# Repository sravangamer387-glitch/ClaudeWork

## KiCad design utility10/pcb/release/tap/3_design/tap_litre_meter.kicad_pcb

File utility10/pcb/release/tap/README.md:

# Tap Litre Meter - main board (rev B)

Tap litre meter: hall flow sensor, pulse counting, OLED display, target alarm, 3 x AA.

**Status: engineering release, software-verified only (ERC on the netlist, KiCad DRC, netlist cross-check, SPICE where noted). Not yet built, not reviewed by a second engineer, not certified.**

## Specification
- Board 68 x 46 mm, 2 layers, 1.6 mm FR-4, 1 oz copper, rounded corners R2.5 mm, 4 x M2.5 mounting holes, 2 fiducials.
- Rules used: min track 0.2 mm (power 0.4 mm), min clearance 0.2 mm, via 0.6/0.3 mm, GND pour on both layers, 69 stitching vias.
- Finish: ENIG recommended (HASL lead-free acceptable); green mask, white silk; IPC class 2.
- 28 parts, 19 nets.

## Circuit description
- Flow pulses on INT1 (PD3) with 10 k pull-up, 100 nF filter, 1 k series and TVS on the cable; OLED on I2C (4.7 k pull-ups) through a 4-pin JST.
- **The flow sensor must accept 3.5-24 V** (3 x AA falls to 3.6 V); calibrate pulses per litre with a 10 L bucket.

## Power
Idle in power-down, wake on pulses; display only while water flows plus 10 s: months of battery.

## Verification
| Check | Result |
|---|---|
| Electrical rule check on the netlist (own ERC: unconnected pins, single-pin nets, output conflicts, unpowered supplies, symbol/footprint pin match) | 0 errors, 0 warnings |
| KiCad DRC | 0 errors, 0 warnings; unconnected pads: 0 |
| Schematic netlist equals PCB netlist | yes |
| Router failures | 0 |
| 3D STEP export | yes |
| Independent Gerber parse (gerbonara): layers parsed, outline size equals the design | 9 layers, outline [68.1, 46.1] mm, match |

Enclosure (prototype shell for 3D printing): outer 84.0 x 74.3 x 39.8 mm, collision/opening check: pass

## Bill of materials
| Ref | Value | Footprint | Manufacturer part | LCSC # | LCSC status |
|---|---|---|---|---|---|
| U1 | ATmega328P-AU | TQFP-32_7x7mm_P0.8mm | ATMEGA328P-AU | C14877 | verified |
| C1 | 100n | C_0603_1608Metric | Samsung CL10B104KB8NNNC 0603 100nF X7R 50V | C1591 | verified |
| C2 | 100n | C_0603_1608Metric | Samsung CL10B104KB8NNNC 0603 100nF X7R 50V | C1591 | verified |
| C3 | 100n | C_0603_1608Metric | Samsung CL10B104KB8NNNC 0603 100nF X7R 50V | C1591 | verified |
| R7 | 10k | R_0603_1608Metric | 0603 10k 1% | C25804 | verified |
| J2 | ISP | PinHeader_2x03_P2.54mm_Vertical | HCTL PZ254-2-03-Z-8.5 (ZHOURI C5116479 had only 340 in stock) | C2894964 | verified |
| J1 | BATT 3xAA | JST_PH_B2B-PH-K_1x02_P2.00mm_Vertical | JST B2B-PH-K-S(LF)(SN) | C131337 | verified |
| SW1 | Power | SW_SPDT_PCM12 | C&K PCM12SMTR | C221841 | verified |
| Q2 | AO3401A | SOT-23 | AO3401A | C15127 | verified |
| C4 | 10u | C_0805_2012Metric | 0805 10uF X5R | C15850 | verified |
| BZ1 | Buzzer | Buzzer_12x9.5RM7.6 | YUEXIN KC1206 16 ohm passive magnetic 12x9.5 mm (2048 Hz) | C781869 | verified |
| Q1 | MMBT3904 | SOT-23 | MMBT3904 | C20526 | verified |
| D2 | 1N4148WS | D_SOD-323 | 1N4148WS | C2128 | verified |
| R6 | 1k | R_0603_1608Metric | 0603 1k 1% | C21190 | verified |
| D1 | Green | LED_0603_1608Metric | Hubei KENTO KT-0603YG yellow-green 570 nm, Vf about 2 V (lights well from 3.3 V with 1 k; the Everlight 19-217 green was out of stock) | C2289 | verified |
| R5 | 1k | R_0603_1608Metric | 0603 1k 1% | C21190 | verified |
| SW2 | Reset / target | SW_SPST_B3U-1000P | Omron B3U-1000P | C231329 | verified |
| J3 | Flow sensor | JST_PH_B3B-PH-K_1x03_P2.00mm_Vertical | JST B3B-PH-K-S(LF)(SN) | C131339 | verified |
| R8 | 1k | R_0603_1608Metric | 0603 1k 1% | C21190 | verified |
| R9 | 10k | R_0603_1608Metric | 0603 10k 1% | C25804 | verified |
| C9 | 100n | C_0603_1608Metric | Samsung CL10B104KB8NNNC 0603 100nF X7R 50V | C1591 | verified |
| D4 | TVS 5V bidir | D_SOD-323 | Nexperia PESD5V0S1BA,115 | C19224 | verified |
| J4 | OLED 0.91in I2C | JST_PH_B4B-PH-K_1x04_P2.00mm_Vertical | JST B4B-PH-K-S(LF)(SN) | C131334 | verified |
| R10 | 4.7k | R_0603_1608Metric | 0603 4.7k 1% | C23162 | verified |
| R11 | 4.7k | R_0603_1608Metric | 0603 4.7k 1% | C23162 | verified |
| TP1 | TP | TestPoint_Pad_D1.5mm |  |  |  |
| TP2 | TP | TestPoint_Pad_D1.5mm |  |  |  |
| TP3 | TP | TestPoint_Pad_D1.5mm |  |  |  |

`verified` = LCSC number confirmed by web search on 2026-10-31/11-01; `memory` = from my recollection, **check on lcsc.com before ordering**; empty = no number chosen (through-hole connectors, switches, buzzer, test points: hand-assembled or chosen by the buyer). `*_JLC_BOM.csv` / `*_JLC_CPL.csv` list only the parts with an LCSC number; JLCPCB rotation corrections (CPL) must be checked in their viewer.

## Assembly notes
- Reflow (JLCPCB SMT): all SMD parts with an LCSC number. Hand-solder: JST connectors, pin headers, buzzer, switches, test points as listed in the BOM. Fiducials and mounting holes are in the Gerbers.
- Polarity: LED cathode toward GND (silk marks), electrolytic none, diode D2 cathode to +V, Q2 orientation as footprint (SOT-23 pin 1 = gate).
- Programming: ISP header J2 (pin 1 = MISO, square pad). Flash the matching image from `utility10/firmware/release/`: Seeti Counter `4MHz/seeti_prod.hex` (production firmware: timer-triggered 16 kS/s ADC, scan mode to find the real whistle frequency, battery check), Rain Alert `8MHz/rain_alert.hex`, Bijli Meter Reader `8MHz/bijli_meter.hex` (demo-grade firmware, to be hardened).

## Bring-up and test
1. Blow/spin the sensor: FLOW (TP3) pulses; firmware counts.
2. Run 10 L from a calibrated bucket: adjust pulses-per-litre.

## Files
`1_fabrication/` Gerber + drill zip (upload to JLCPCB/any fab), fab notes, copper plot
`2_assembly/` JLC BOM + CPL (SMD parts JLC assembles), full BOM with LCSC numbers for every part, pick-and-place, assembly drawing
`3_design/` KiCad 7 project (pcb, schematic, libs), netlist, STEP model, schematic PDF, renders
`4_enclosure/` printable enclosure (base, screwed lid, battery door, plungers / light pipes / switch extensions) or a mounting plate for a bought IP65 box; dimensions and notes in enclosure.json
`5_verification/` DRC, ERC, verification and readiness reports

## Known limits and review checklist
- Layout was produced by a custom router and software placement; a human layout review (analog routing, ground returns, creepage, connector mechanics, silkscreen) is still required.
- Not verified: EMC, ESD (apart from TVS parts where fitted), thermal, real component tolerances, supplier stock/price, assembly house design-for-manufacture check (run JLCPCB's DFM check on the Gerbers).
- Firmware thresholds are placeholders to be calibrated on prototypes.

## Manufacturing readiness (automatic check)

| Check | Result |
|---|---|
| gerber layers and drill present | PASS |
| drc errors 0 | PASS |
| unconnected 0 | PASS |
| netlist matches schematic | PASS |
| erc errors 0 | PASS |
| independent gerber check clean | PASS |
| every part has lcsc number | PASS |
| every lcsc number verified | PASS |
| cpl rows equal jlc bom parts | PASS |
| step model | PASS |
| KiCad DRC warnings | 0 |
| **Order ready** | **YES** |

Order steps: (1) upload `1_fabrication/*_gerbers.zip`; (2) for assembly upload `2_assembly/*_JLC_BOM.csv` and `*_JLC_CPL.csv`, check the 3D/rotation preview for every polarised part (diodes, ICs, LEDs, electrolytics) because CPL rotations are generated, not hand-checked; (3) buy the through-hole parts listed in `*_BOM_full.csv` marked hand/THT and solder them; (4) re-check stock and the exact LCSC listing for every line before paying.

Limits: the layout is software-generated and has not been reviewed by a PCB engineer; no prototype has been built; the first batch should be treated as a prototype run (order 5 boards).

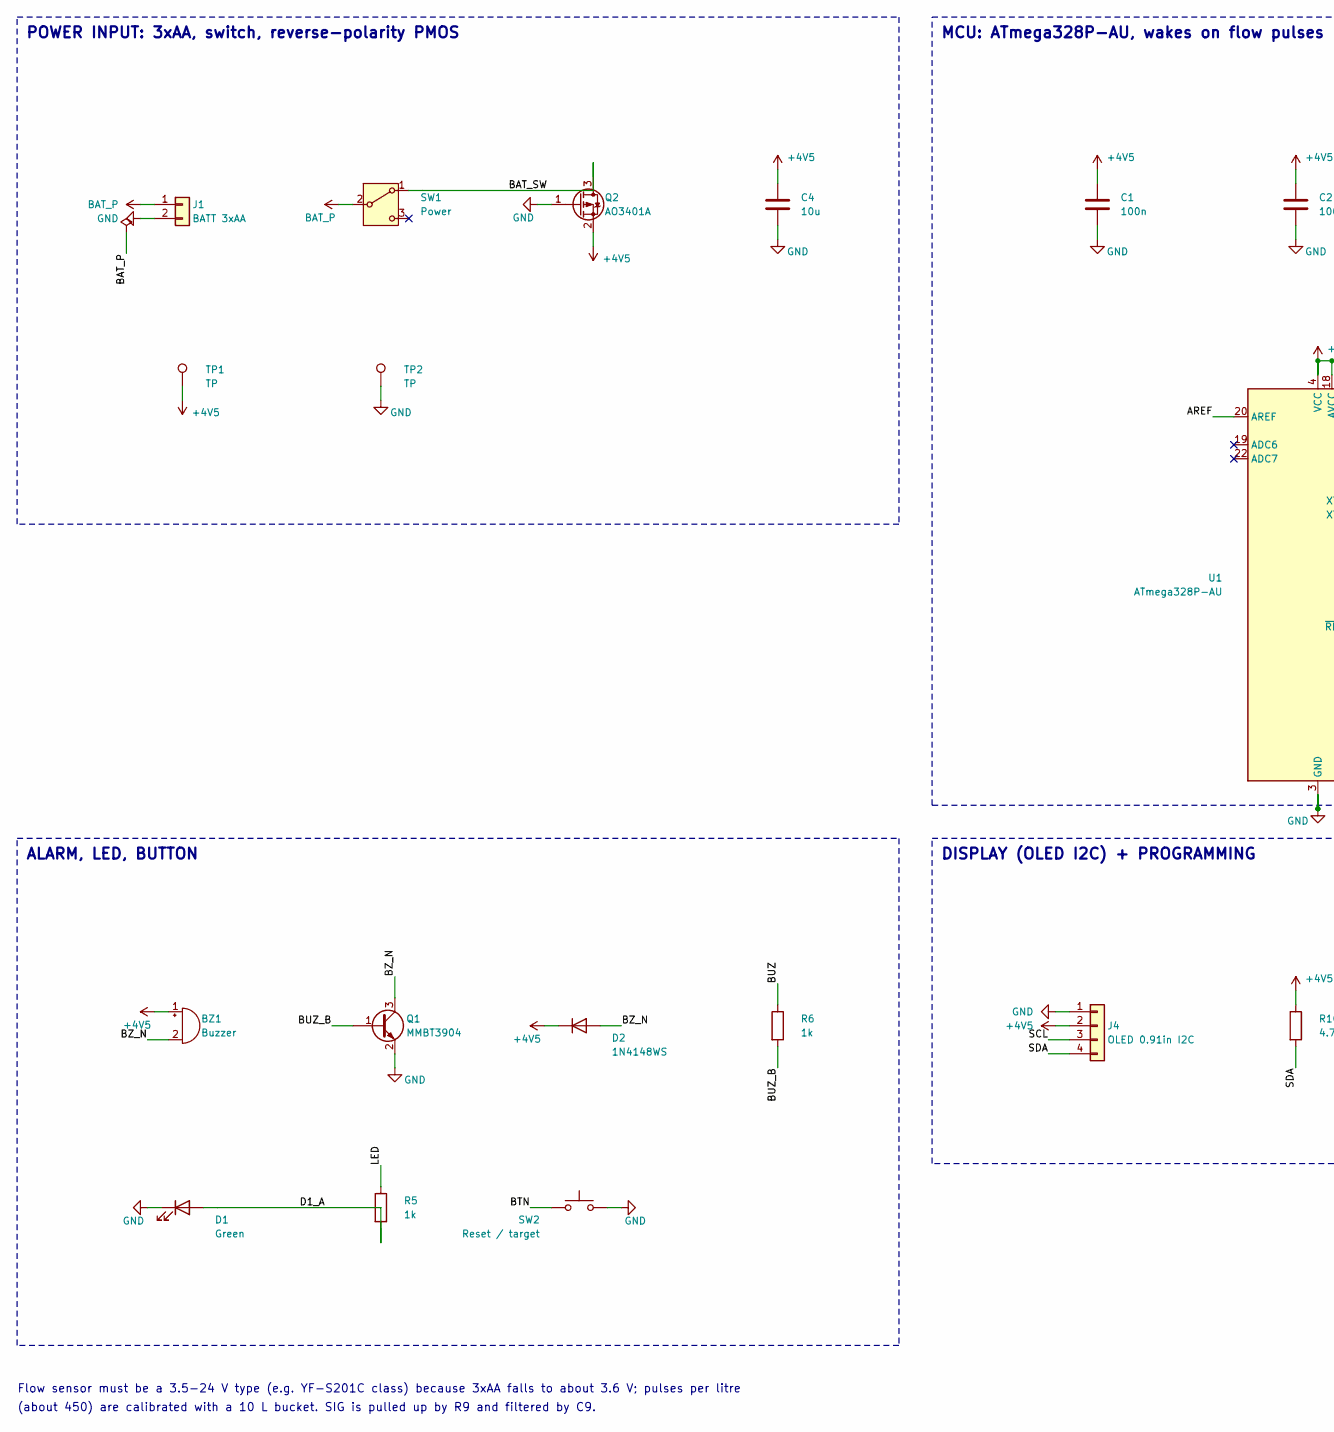
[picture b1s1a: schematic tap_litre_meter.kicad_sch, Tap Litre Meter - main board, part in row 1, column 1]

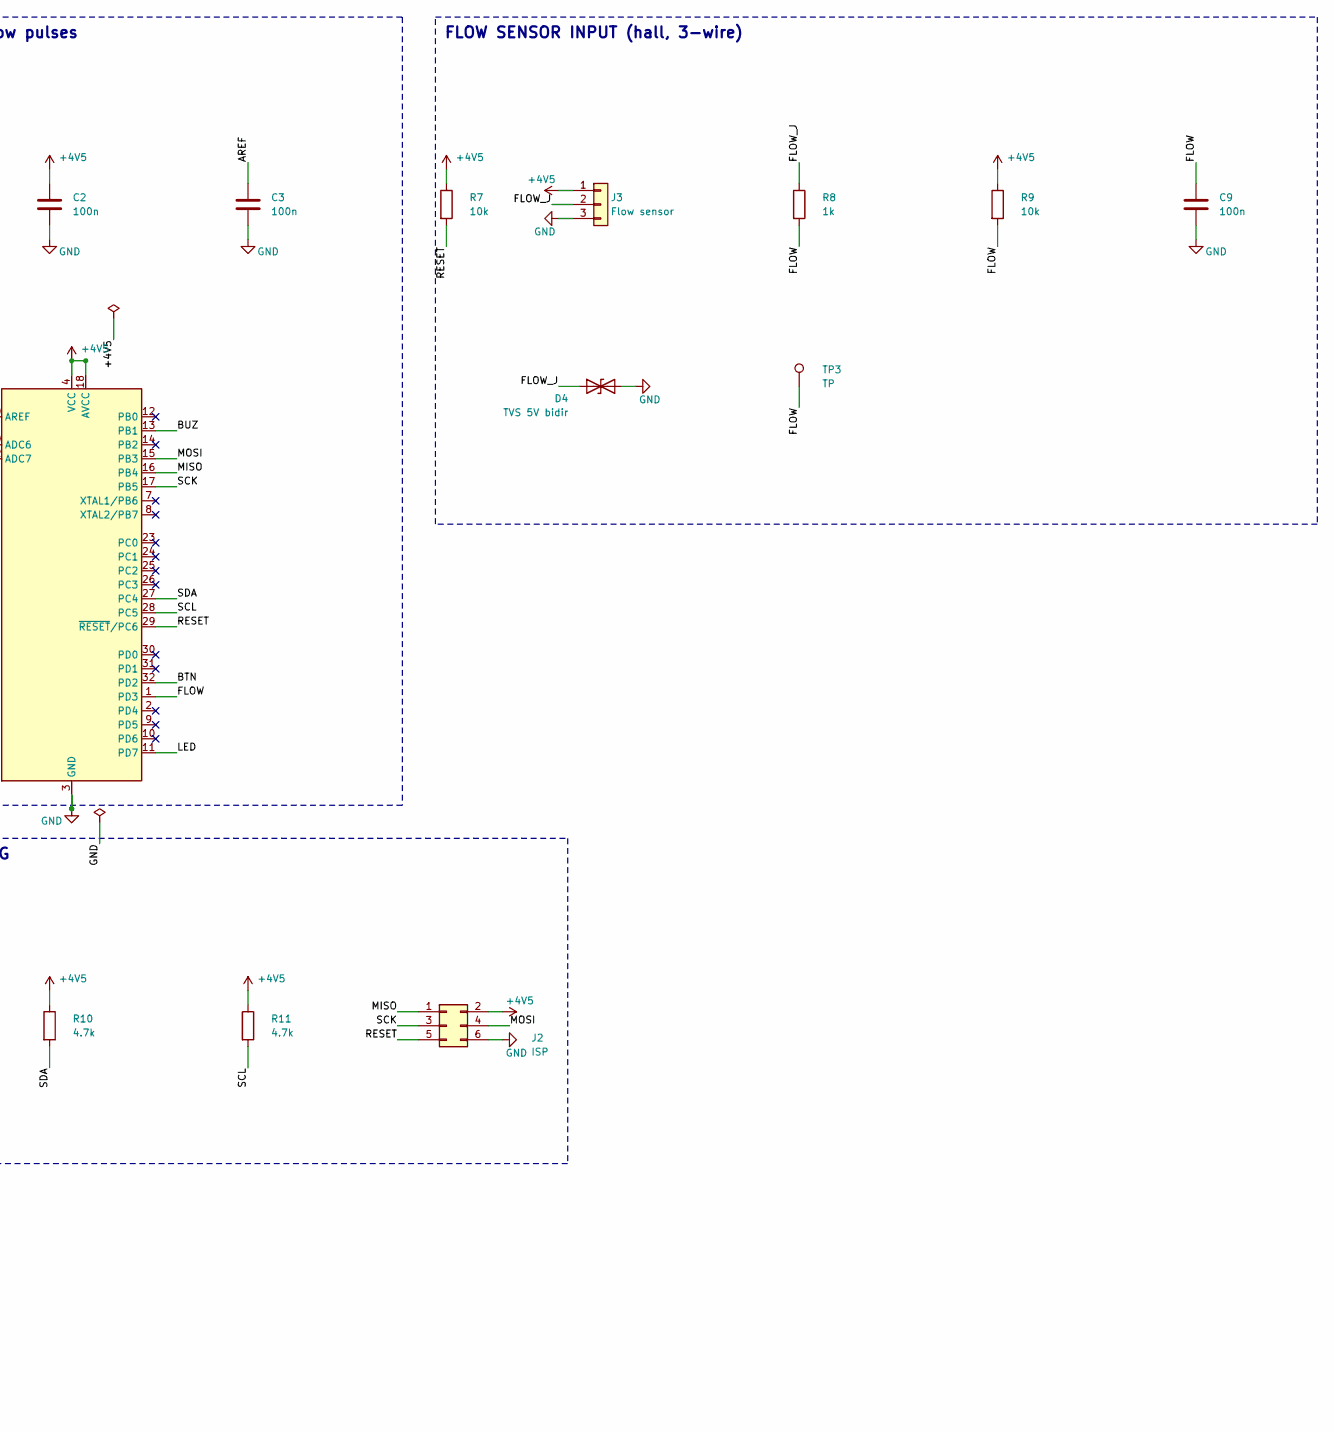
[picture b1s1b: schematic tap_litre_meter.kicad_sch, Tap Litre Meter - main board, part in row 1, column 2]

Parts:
BZ1: Buzzer; Buzzer_12x9.5RM7.6
C1, C2, C3, C9: 100n; C_0603_1608Metric
C4: 10u; C_0805_2012Metric
D1: Green; LED_0603_1608Metric
D2: 1N4148WS; D_SOD-323
D4: TVS 5V bidir; D_SOD-323
J1: BATT 3xAA; JST_PH_B2B-PH-K_1x02_P2.00mm_Vertical
J2: ISP; PinHeader_2x03_P2.54mm_Vertical
J3: Flow sensor; JST_PH_B3B-PH-K_1x03_P2.00mm_Vertical
J4: OLED 0.91in I2C; JST_PH_B4B-PH-K_1x04_P2.00mm_Vertical
Q1: MMBT3904; SOT-23
Q2: AO3401A; SOT-23
R5, R6, R8: 1k; R_0603_1608Metric
R7, R9: 10k; R_0603_1608Metric
R10, R11: 4.7k; R_0603_1608Metric
SW1: Power; SW_SPDT_PCM12
SW2: Reset / target; SW_SPST_B3U-1000P
TP1, TP2, TP3: TP; TestPoint_Pad_D1.5mm
U1: ATmega328P-AU; TQFP-32_7x7mm_P0.8mm

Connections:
+4V5: BZ1.1 (+), C1.1, C2.1, C4.1, D2.1 (K), J2.2, J3.1, J4.2, Q2.2 (S), R7.1, R9.1, R10.1, R11.1, TP1.1, U1.4 (VCC), U1.6 (VCC), U1.18 (AVCC)
AREF: C3.1, U1.20 (AREF)
BAT_P: J1.1, SW1.2 (B)
BAT_SW: Q2.3 (D), SW1.1 (A)
BTN: SW2.1, U1.32 (PD2)
BUZ: R6.1, U1.13 (PB1)
BUZ_B: Q1.1 (B), R6.2
BZ_N: BZ1.2 (-), D2.2 (A), Q1.3 (C)
D1_A: D1.2 (A), R5.2
FLOW: C9.1, R8.2, R9.2, TP3.1, U1.1 (PD3)
FLOW_J: D4.1 (A1), J3.2, R8.1
GND: C1.2, C2.2, C3.2, C4.2, C9.2, D1.1 (K), D4.2 (A2), J1.2, J2.6, J3.3, J4.1, Q1.2 (E), Q2.1 (G), SW2.2, TP2.1, U1.3 (GND), U1.5 (GND), U1.21 (GND)
LED: R5.1, U1.11 (PD7)
MISO: J2.1, U1.16 (PB4)
MOSI: J2.4, U1.15 (PB3)
RESET: J2.5, R7.2, U1.29 (~RESET/PC6)
SCK: J2.3, U1.17 (PB5)
SCL: J4.3, R11.2, U1.28 (PC5)
SDA: J4.4, R10.2, U1.27 (PC4)

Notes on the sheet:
POWER INPUT: 3xAA, switch, reverse-polarity PMOS
MCU: ATmega328P-AU, wakes on flow pulses
FLOW SENSOR INPUT (hall, 3-wire)
ALARM, LED, BUTTON
DISPLAY (OLED I2C) + PROGRAMMING
Flow sensor must be a 3.5-24 V type (e.g. YF-S201C class) because 3xAA falls to about 3.6 V; pulses per litre
(about 450) are calibrated with a 10 L bucket. SIG is pulled up by R9 and filtered by C9.

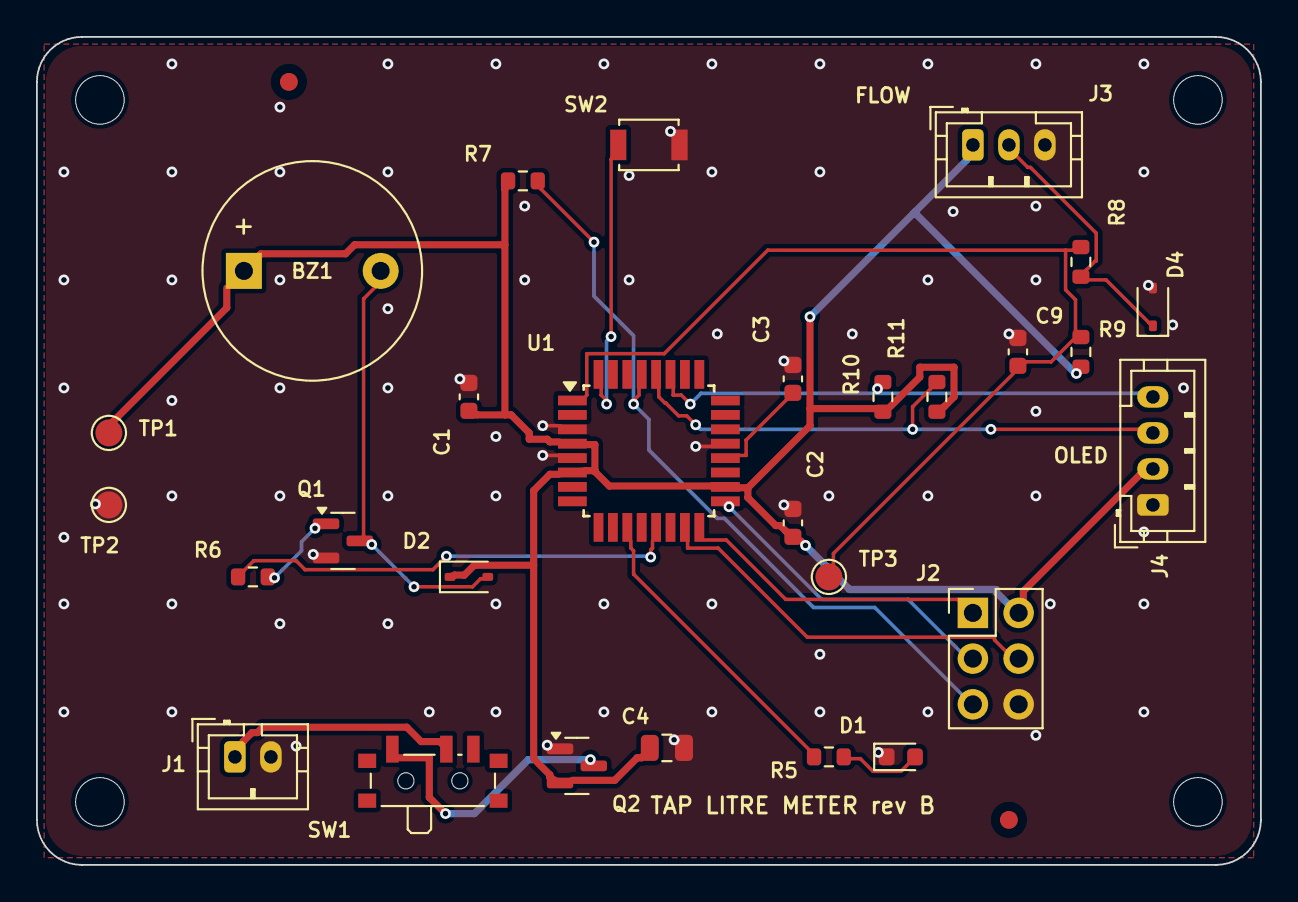
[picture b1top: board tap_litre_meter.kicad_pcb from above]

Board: 2 copper layers, 68.0 x 46.0 mm, 34 parts (0 on the bottom side), 19 nets.

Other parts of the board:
FID1, FID2: Fiducial; Fiducial_1mm_Mask2mm
H1, H2, H3, H4: M2.5; MountingHole_2.7mm_M2.5

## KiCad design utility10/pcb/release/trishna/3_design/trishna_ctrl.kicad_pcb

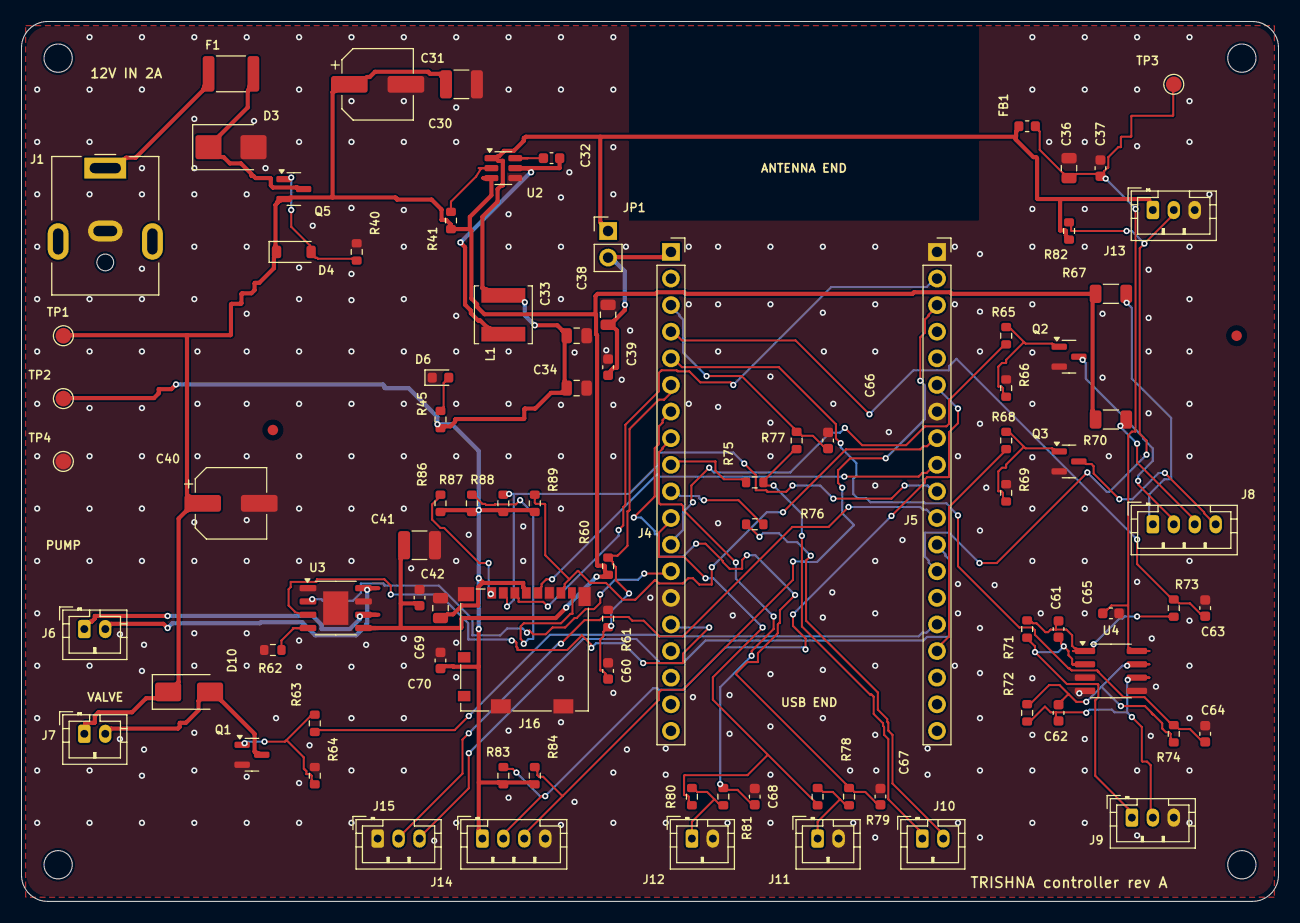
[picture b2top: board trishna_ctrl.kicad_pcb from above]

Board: 2 copper layers, 120.0 x 84.0 mm, 94 parts (0 on the bottom side), 56 nets.

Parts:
C30, C40: 100u/35V; CP_Elec_6.3x7.7
C31, C41: 10u/50V; C_1210_3225Metric
C32, C37, C39, C42, C60, C65, C70: 100n; C_0603_1608Metric
C33, C34: 22u/10V; C_0805_2012Metric
C36, C38, C69: 10u; C_0805_2012Metric
C61, C63, C64: 10n; C_0603_1608Metric
C62, C66, C67, C68: 1n; C_0603_1608Metric
D3: SMBJ15A; D_SMB
D4: BZT52C12; D_SOD-123
D6: Green; LED_0603_1608Metric
D10: M7 (1N4007); D_SMA
F1: PTC 2A 16V; Fuse_1812_4532Metric
FB1: BLM18 600R; L_0603_1608Metric
FID1, FID2: Fiducial; Fiducial_1mm_Mask2mm
H1, H2, H3, H4: M2.5; MountingHole_2.7mm_M2.5
J1: 12 V DC in (2 A); BarrelJack_CUI_PJ-063AH_Horizontal
J4: DevKitC left: 3V3 EN 36 39 34 35 32 33 25 26 27 1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; PinSocket_1x19_P2.54mm_Vertical
J5: DevKitC right: GND 23 22 TX RX 21 GND 19 18 5 17 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; PinSocket_1x19_P2.54mm_Vertical
J6: Peristaltic pump 12 V (red = PUMP_O1); JST_PH_B2B-PH-K_1x02_P2.00mm_Vertical
J7: Solenoid valve 12 V NC; JST_PH_B2B-PH-K_1x02_P2.00mm_Vertical
J8: Sensor-block LEDs (450 nm blue, 850 nm IR); JST_PH_B4B-PH-K_1x04_P2.00mm_Vertical
J9: Photodiodes BPW34: transmission, 90-degree scatte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; JST_PH_B3B-PH-K_1x03_P2.00mm_Vertical
J10: EC electrodes (titanium pins E1, E2); JST_PH_B2B-PH-K_1x02_P2.00mm_Vertical
J11: Sump stream-detect probe; JST_PH_B2B-PH-K_1x02_P2.00mm_Vertical
J12: Chamber-B floor leak probe; JST_PH_B2B-PH-K_1x02_P2.00mm_Vertical
J13: DS18B20 temperature probe; JST_PH_B3B-PH-K_1x03_P2.00mm_Vertical
J14: VL53L1X ToF presence sensor (I2C); JST_PH_B4B-PH-K_1x04_P2.00mm_Vertical
J15: Telemetry UART (ESP32 TX out, RX in) to USB-serial; JST_PH_B3B-PH-K_1x03_P2.00mm_Vertical
J16: microSD (SPI log); microSD_HC_Molex_104031-0811
JP1: 3V3 link (remove for USB-only power); PinHeader_1x02_P2.54mm_Vertical
L1: 4.7u; L_Changjiang_FNR5040S
Q1, Q2, Q3: AO3400A; SOT-23
Q5: AO3401A; SOT-23
R40, R61, R71, R86, R87, R88, R89: 10k; R_0603_1608Metric
R41, R60, R64, R66, R69: 100k; R_0603_1608Metric
R45, R73, R74, R79, R81: 1k; R_0603_1608Metric
R62, R80: 47k; R_0603_1608Metric
R63, R65, R68, R76, R77: 100; R_0603_1608Metric
R67, R70: 1k 1/4W; R_1206_3216Metric
R72: 1M; R_0603_1608Metric
R75: 330; R_0603_1608Metric
R78, R82, R83, R84: 4.7k; R_0603_1608Metric
TP1, TP2, TP3, TP4: TP; TestPoint_Pad_D1.5mm
U2: AP63203WU-7; TSOT-23-6
U3: DRV8871DDAR; HTSOP-8-1EP_3.9x4.9mm_P1.27mm_EP2.4x3.2mm
U4: MCP6002T-I/SN; SOIC-8_3.9x4.9mm_P1.27mm

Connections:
+3V3: C33.1, C34.1, C69.1, C70.1, FB1.1, J13.1, J14.1, J16.4, JP1.1, L1.2, R45.1, R82.1, R83.1, R84.1, R86.1, R87.1, R88.1, R89.1, TP2.1, U2.1
+3V3A: C36.1, C37.1, C65.1, FB1.2, TP3.1, U4.8
BST: C32.1, U2.6
DK3V3: C38.1, C39.1, J4.1, JP1.2
EC_ADC: C66.1, J4.3, R77.2
EC_DRV_A: J4.9, R75.1
EC_DRV_B: J4.10, R76.2
EC_E2: J10.2, R76.1
EC_N1: J10.1, R75.2, R77.1
EN_B: R41.2, U2.2
GATE: D4.2, Q5.1, R40.1
GND: C30.2, C31.2, C33.2, C34.2, C36.2, C37.2, C38.2, C39.2, C40.2, C41.2, C42.2, C60.2, C63.2, C64.2, C65.2, C66.2, C67.2, C68.2, C69.2, C70.2, D3.2, D6.1, J1.2, J4.14, J5.1, J5.7, J9.3, J11.2, J12.2, J13.3, J14.4, J15.1, J16.6, J16.11, Q1.2, Q2.2, Q3.2, R40.2, R61.2, R62.2, R64.2, R66.2, R69.2, TP4.1, U2.4, U3.1, U3.7, U3.9, U4.3, U4.4, U4.5
ILIM: R62.1, U3.4
LEAK_ADC: C68.1, J4.8, R81.2
LEAK_P: J12.1, R80.2, R81.1
LEDB_A: J8.1, R67.2
LEDB_GR: Q2.1, R65.2, R66.1
LEDB_K: J8.2, Q2.3
LEDI_A: J8.3, R70.2
LEDI_GR: Q3.1, R68.2, R69.1
LEDI_K: J8.4, Q3.3
LED_A: D6.2, R45.2
LED_BLU: J4.12, R65.1
LED_IR: J5.16, R68.1
LVL_DRV: J4.11, R78.1, R80.1
ONEWIRE: J5.13, J13.2, R82.2
OPT_SC_ADC: C64.1, J4.5, R74.2
OPT_TX_ADC: C63.1, J4.4, R73.2
PD_SC: C62.1, J9.2, R72.1, U4.6
PD_TX: C61.1, J9.1, R71.1, U4.2
PUMP_IN1: J4.15, U3.3
PUMP_IN2: J4.13, U3.2
PUMP_O1: J6.1, U3.6
PUMP_O2: J6.2, U3.8
SCL: J5.3, J14.3, R84.2
SC_OUT: C62.2, R72.2, R74.1, U4.7
SDA: J5.6, J14.2, R83.2
SD_CS: J5.10, J16.2, R88.2
SD_DAT1: J16.8, R87.2
SD_DAT2: J16.1, R86.2
SD_MISO: J5.8, J16.7, R89.2
SD_MOSI: J5.2, J16.3
SD_SCK: J5.9, J16.5
SUMP_ADC: C67.1, J4.7, R79.2
SUMP_P: J11.1, R78.2, R79.1
SW: C32.2, L1.1, U2.5
TLM_RX: J5.12, J15.3
TLM_TX: J5.11, J15.2
TX_OUT: C61.2, R71.2, R73.1, U4.1
VALVE: J5.15, R63.1
VALVE_D: D10.2, J7.2, Q1.3
VALVE_GR: Q1.1, R63.2, R64.1
VIN12: F1.1, J1.1
VIN_ADC: C60.1, J4.6, R60.2, R61.1
VIN_F: D3.1, F1.2, Q5.3
VM: C30.1, C31.1, C40.1, C41.1, C42.1, D4.1, D10.1, J7.1, Q5.2, R41.1, R60.1, R67.1, R70.1, TP1.1, U2.3, U3.5
